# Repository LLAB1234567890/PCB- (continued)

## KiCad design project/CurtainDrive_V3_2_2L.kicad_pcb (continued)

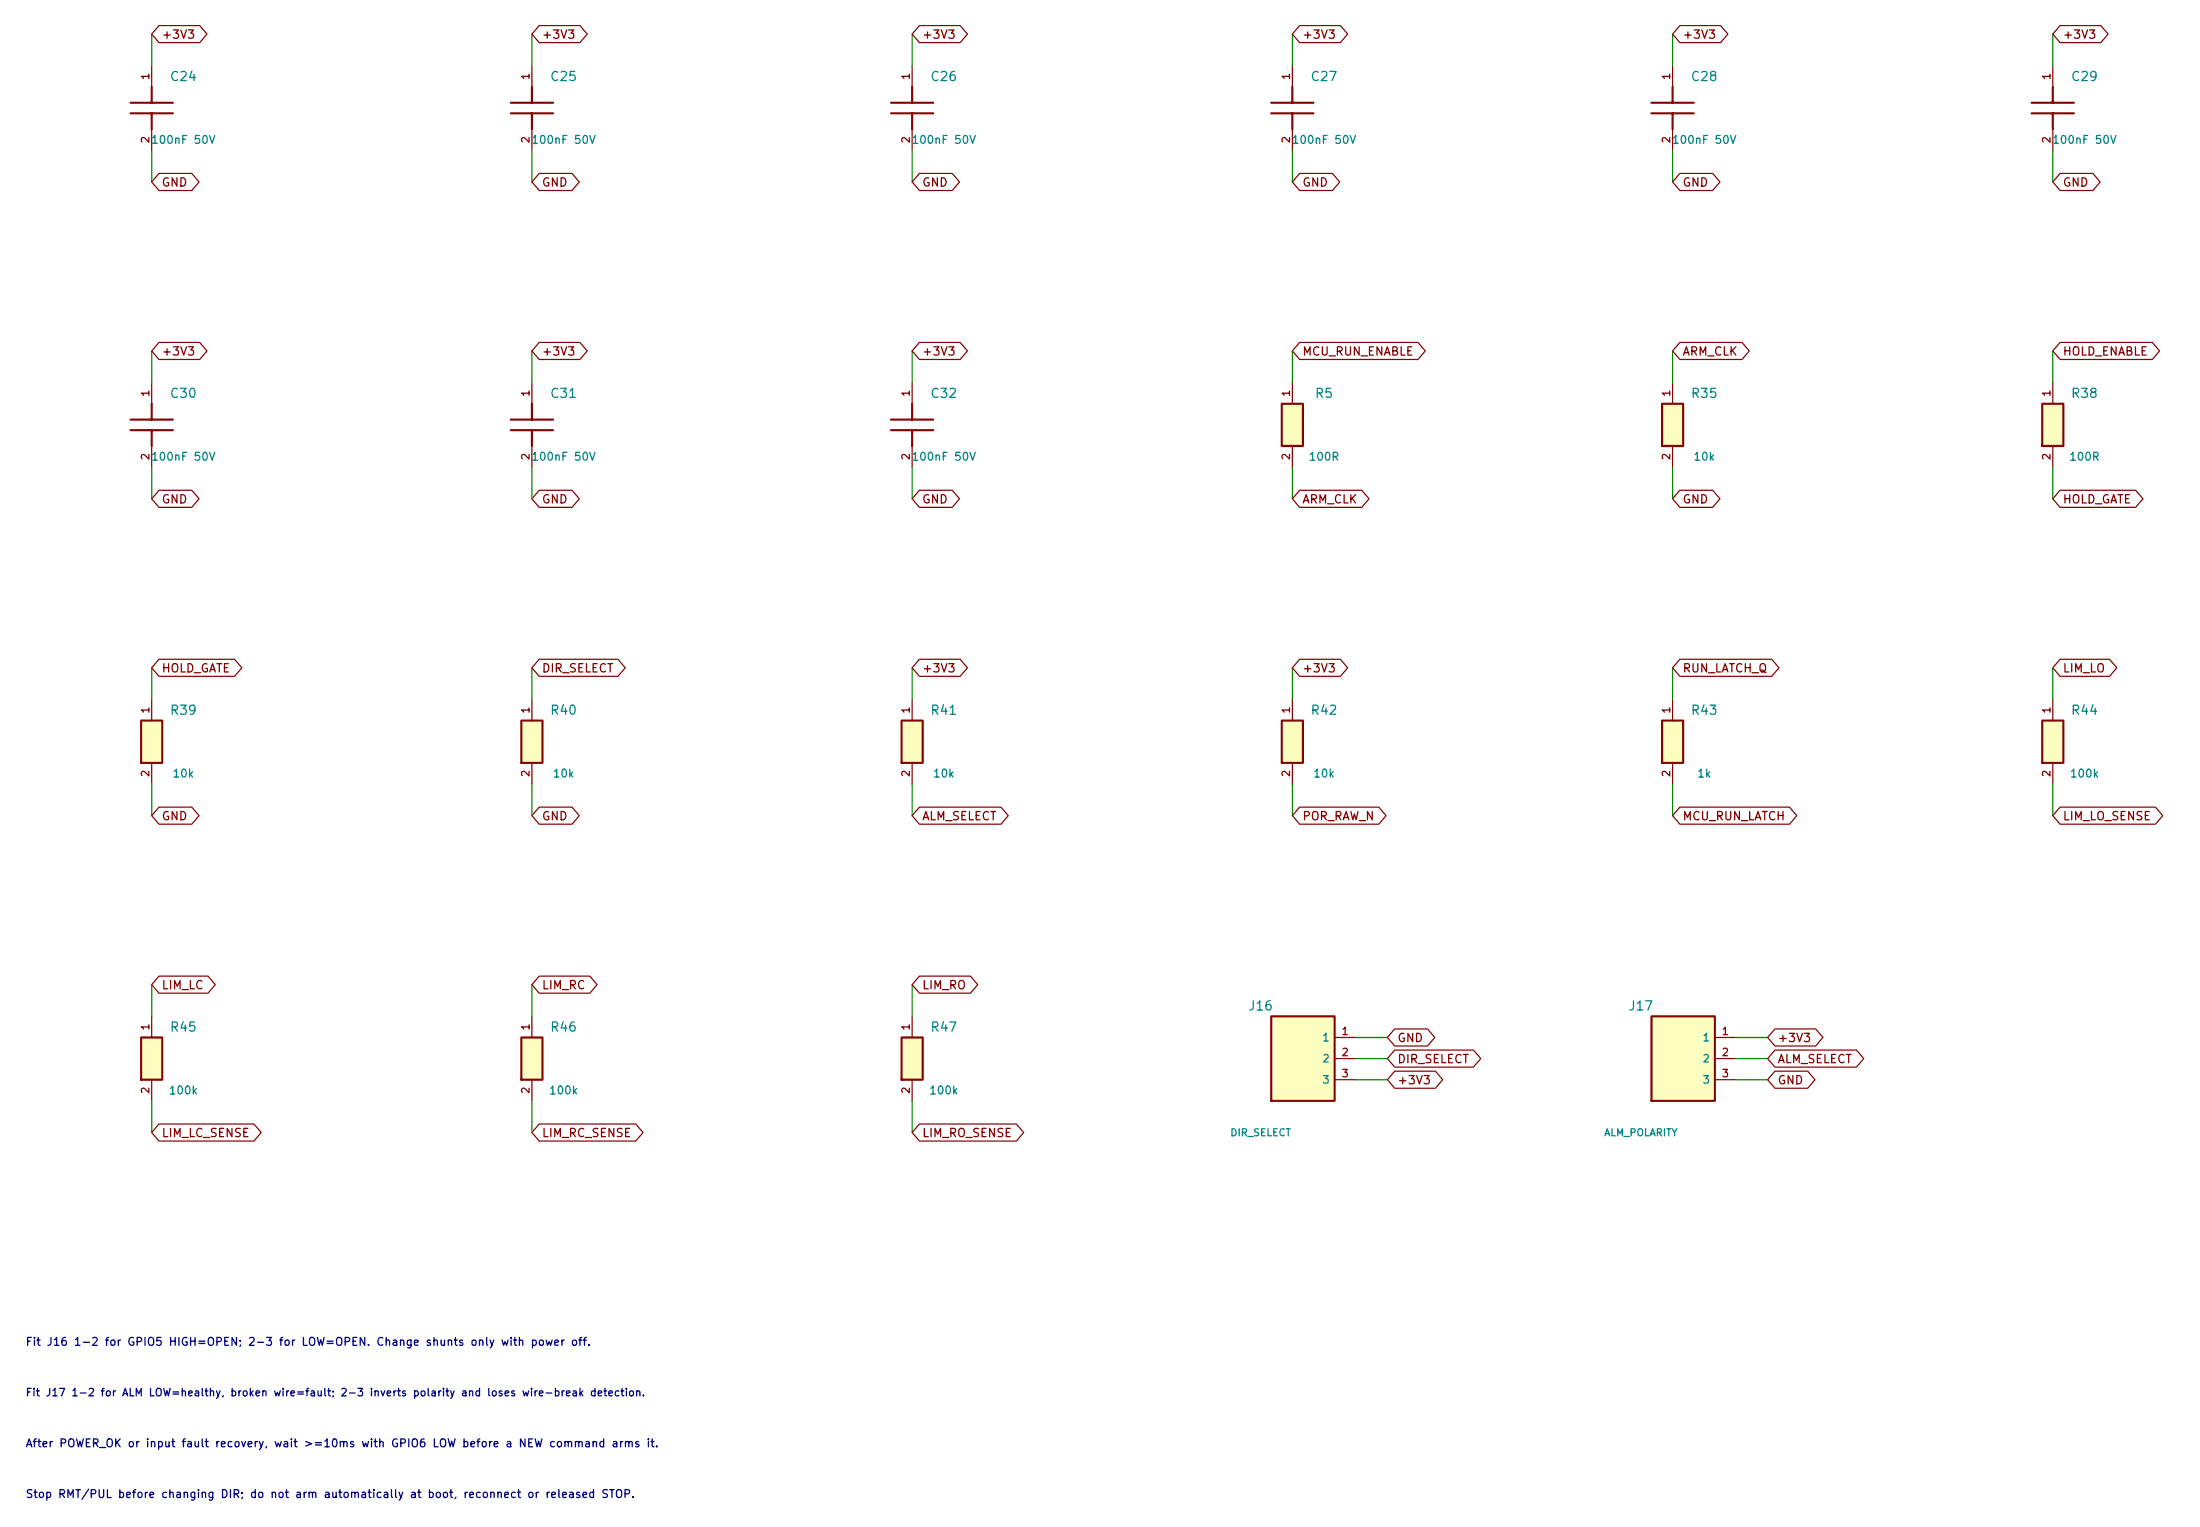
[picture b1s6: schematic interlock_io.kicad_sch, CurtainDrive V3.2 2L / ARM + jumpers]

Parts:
C24, C25, C26, C27, C28, C29, C30, C31, C32: 100nF 50V; C_0603_1608Metric; Voltage Rating 50V / X7R / 10%; Manufacturer Part CC0603KRX7R9BB104
J16: DIR_SELECT; PinHeader_1x03_P2.54mm_Vertical; Voltage Rating 2.54mm pitch; fit matching shunt separa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; Manufacturer Part 2.54mm 1x3 male header - exact MPN TBD
J17: ALM_POLARITY; PinHeader_1x03_P2.54mm_Vertical; Voltage Rating 2.54mm pitch; fit matching shunt separa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; Manufacturer Part 2.54mm 1x3 male header - exact MPN TBD
R5, R38: 100R; R_0603_1608Metric; Voltage Rating 1% / 0.1W; Manufacturer Part 0603WAF1000T5E
R35, R39, R40, R41, R42: 10k; R_0603_1608Metric; Voltage Rating 1% / 0.1W; Manufacturer Part 0603WAF1002T5E
R43: 1k; R_0603_1608Metric; Voltage Rating 1% / 0.1W; Manufacturer Part 0603WAF1001T5E
R44, R45, R46, R47: 100k; R_0603_1608Metric; Voltage Rating 1% / 0.1W; Manufacturer Part 0603WAF1003T5E

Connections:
+3V3: C24.1, C25.1, C26.1, C27.1, C28.1, C29.1, C30.1, C31.1, C32.1, J16.3, J17.1, R41.1, R42.1; also elsewhere on the board
ALM_SELECT: J17.2, R41.2; also elsewhere on the board
ARM_CLK: R5.2, R35.1; also elsewhere on the board
DIR_SELECT: J16.2, R40.1; also elsewhere on the board
GND: C24.2, C25.2, C26.2, C27.2, C28.2, C29.2, C30.2, C31.2, C32.2, J16.1, J17.3, R35.2, R39.2, R40.2; also elsewhere on the board
HOLD_ENABLE: R38.1; also elsewhere on the board
HOLD_GATE: R38.2, R39.1; also elsewhere on the board
LIM_LC: R45.1; also elsewhere on the board
LIM_LC_SENSE: R45.2; also elsewhere on the board
LIM_LO: R44.1; also elsewhere on the board
LIM_LO_SENSE: R44.2; also elsewhere on the board
LIM_RC: R46.1; also elsewhere on the board
LIM_RC_SENSE: R46.2; also elsewhere on the board
LIM_RO: R47.1; also elsewhere on the board
LIM_RO_SENSE: R47.2; also elsewhere on the board
MCU_RUN_ENABLE: R5.1; also elsewhere on the board
MCU_RUN_LATCH: R43.2; also elsewhere on the board
POR_RAW_N: R42.2; also elsewhere on the board
RUN_LATCH_Q: R43.1; also elsewhere on the board

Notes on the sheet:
Stop RMT/PUL before changing DIR; do not arm automatically at boot, reconnect or released STOP.
Fit J16 1-2 for GPIO5 HIGH=OPEN; 2-3 for LOW=OPEN. Change shunts only with power off.
After POWER_OK or input fault recovery, wait >=10ms with GPIO6 LOW before a NEW command arms it.
Fit J17 1-2 for ALM LOW=healthy, broken wire=fault; 2-3 inverts polarity and loses wire-break detection.

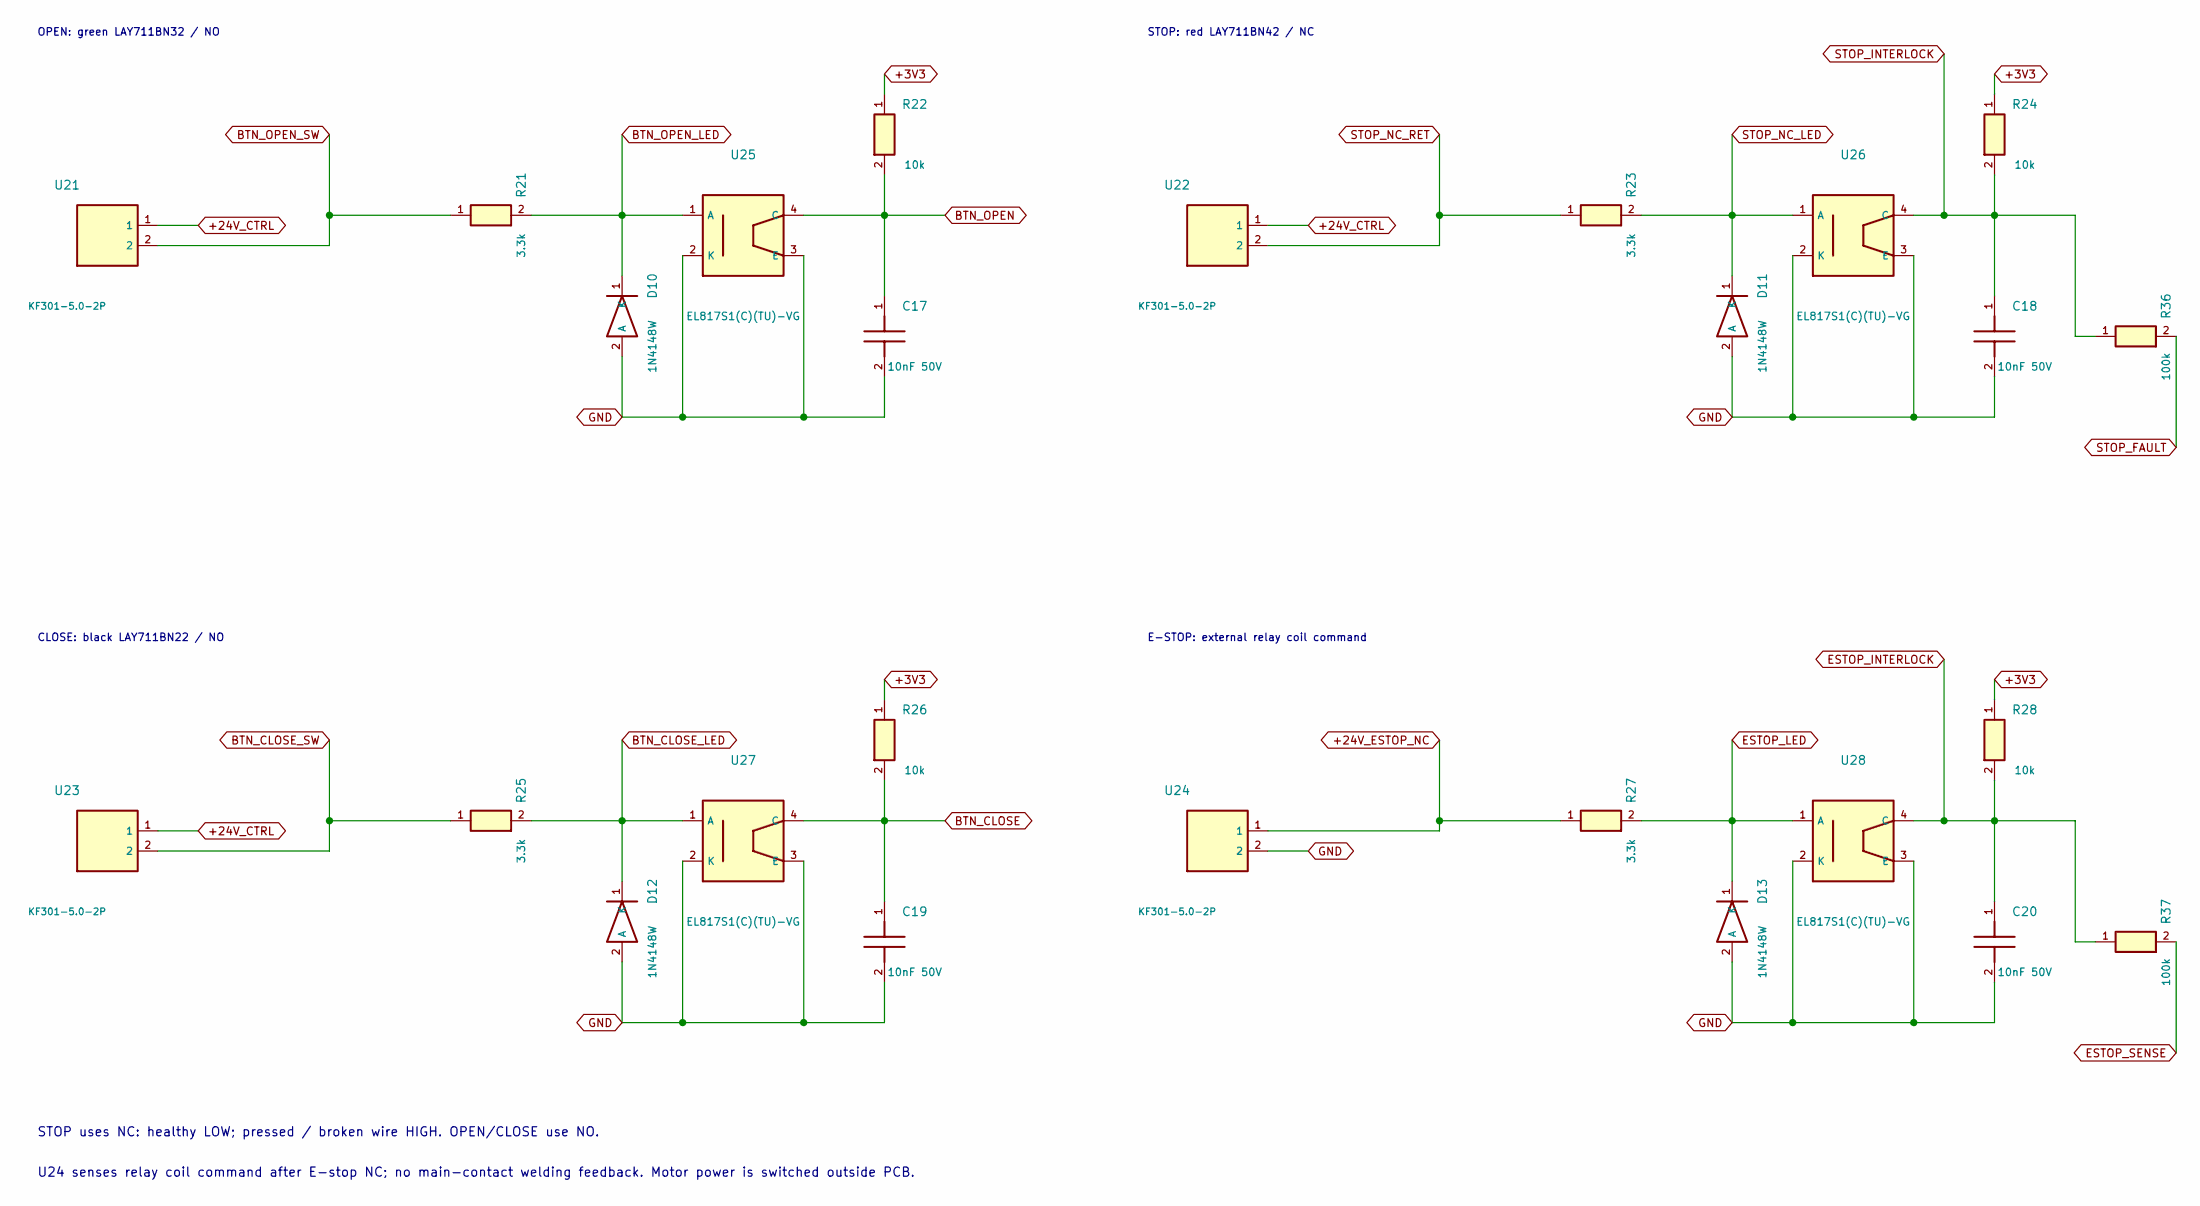
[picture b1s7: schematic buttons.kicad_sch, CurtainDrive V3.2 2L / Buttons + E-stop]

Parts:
C17, C18, C19, C20: 10nF 50V; C_0603_1608Metric; Voltage Rating 50V / X7R / 10%; Manufacturer Part 0603B103K500NT
D10, D11, D12, D13: 1N4148W; D_SOD-123; Voltage Rating 75V / 150mA; Manufacturer Part 1N4148W
R21, R23, R25, R27: 3.3k; R_1210_3225Metric; Voltage Rating 5% / 0.5W; Manufacturer Part 1210W2J0332T5E
R22, R24, R26, R28: 10k; R_0603_1608Metric; Voltage Rating 1% / 0.1W; Manufacturer Part 0603WAF1002T5E
R36, R37: 100k; R_0603_1608Metric; Voltage Rating 1% / 0.1W; Manufacturer Part 0603WAF1003T5E
U21: KF301-5.0-2P; Source_U21; Manufacturer Part KF301-5.0-2P
U22: KF301-5.0-2P; Source_U22; Manufacturer Part KF301-5.0-2P
U23: KF301-5.0-2P; Source_U23; Manufacturer Part KF301-5.0-2P
U24: KF301-5.0-2P; Source_U24; Manufacturer Part KF301-5.0-2P
U25: EL817S1(C)(TU)-VG; Source_U25; Manufacturer Part EL817S1(C)(TU)-VG
U26: EL817S1(C)(TU)-VG; Source_U26; Manufacturer Part EL817S1(C)(TU)-VG
U27: EL817S1(C)(TU)-VG; Source_U27; Manufacturer Part EL817S1(C)(TU)-VG
U28: EL817S1(C)(TU)-VG; Source_U28; Manufacturer Part EL817S1(C)(TU)-VG

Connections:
+3V3: R22.1, R24.1, R26.1, R28.1; also elsewhere on the board
+24V_CTRL: U21.1, U22.1, U23.1; also elsewhere on the board
+24V_ESTOP_NC: R27.1, U24.1
BTN_CLOSE: C19.1, R26.2, U27.4 (C); also elsewhere on the board
BTN_CLOSE_LED: D12.1 (K), R25.2, U27.1 (A)
BTN_CLOSE_SW: R25.1, U23.2
BTN_OPEN: C17.1, R22.2, U25.4 (C); also elsewhere on the board
BTN_OPEN_LED: D10.1 (K), R21.2, U25.1 (A)
BTN_OPEN_SW: R21.1, U21.2
ESTOP_INTERLOCK: C20.1, R28.2, R37.1, U28.4 (C); also elsewhere on the board
ESTOP_LED: D13.1 (K), R27.2, U28.1 (A)
ESTOP_SENSE: R37.2; also elsewhere on the board
GND: C17.2, C18.2, C19.2, C20.2, D10.2 (A), D11.2 (A), D12.2 (A), D13.2 (A), U24.2, U25.2 (K), U25.3 (E), U26.2 (K), U26.3 (E), U27.2 (K), U27.3 (E), U28.2 (K), U28.3 (E); also elsewhere on the board
STOP_FAULT: R36.2; also elsewhere on the board
STOP_INTERLOCK: C18.1, R24.2, R36.1, U26.4 (C); also elsewhere on the board
STOP_NC_LED: D11.1 (K), R23.2, U26.1 (A)
STOP_NC_RET: R23.1, U22.2

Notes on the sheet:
STOP: red LAY711BN42 / NC
U24 senses relay coil command after E-stop NC; no main-contact welding feedback. Motor power is switched outside PCB.
CLOSE: black LAY711BN22 / NO
STOP uses NC: healthy LOW; pressed / broken wire HIGH. OPEN/CLOSE use NO.
E-STOP: external relay coil command
OPEN: green LAY711BN32 / NO

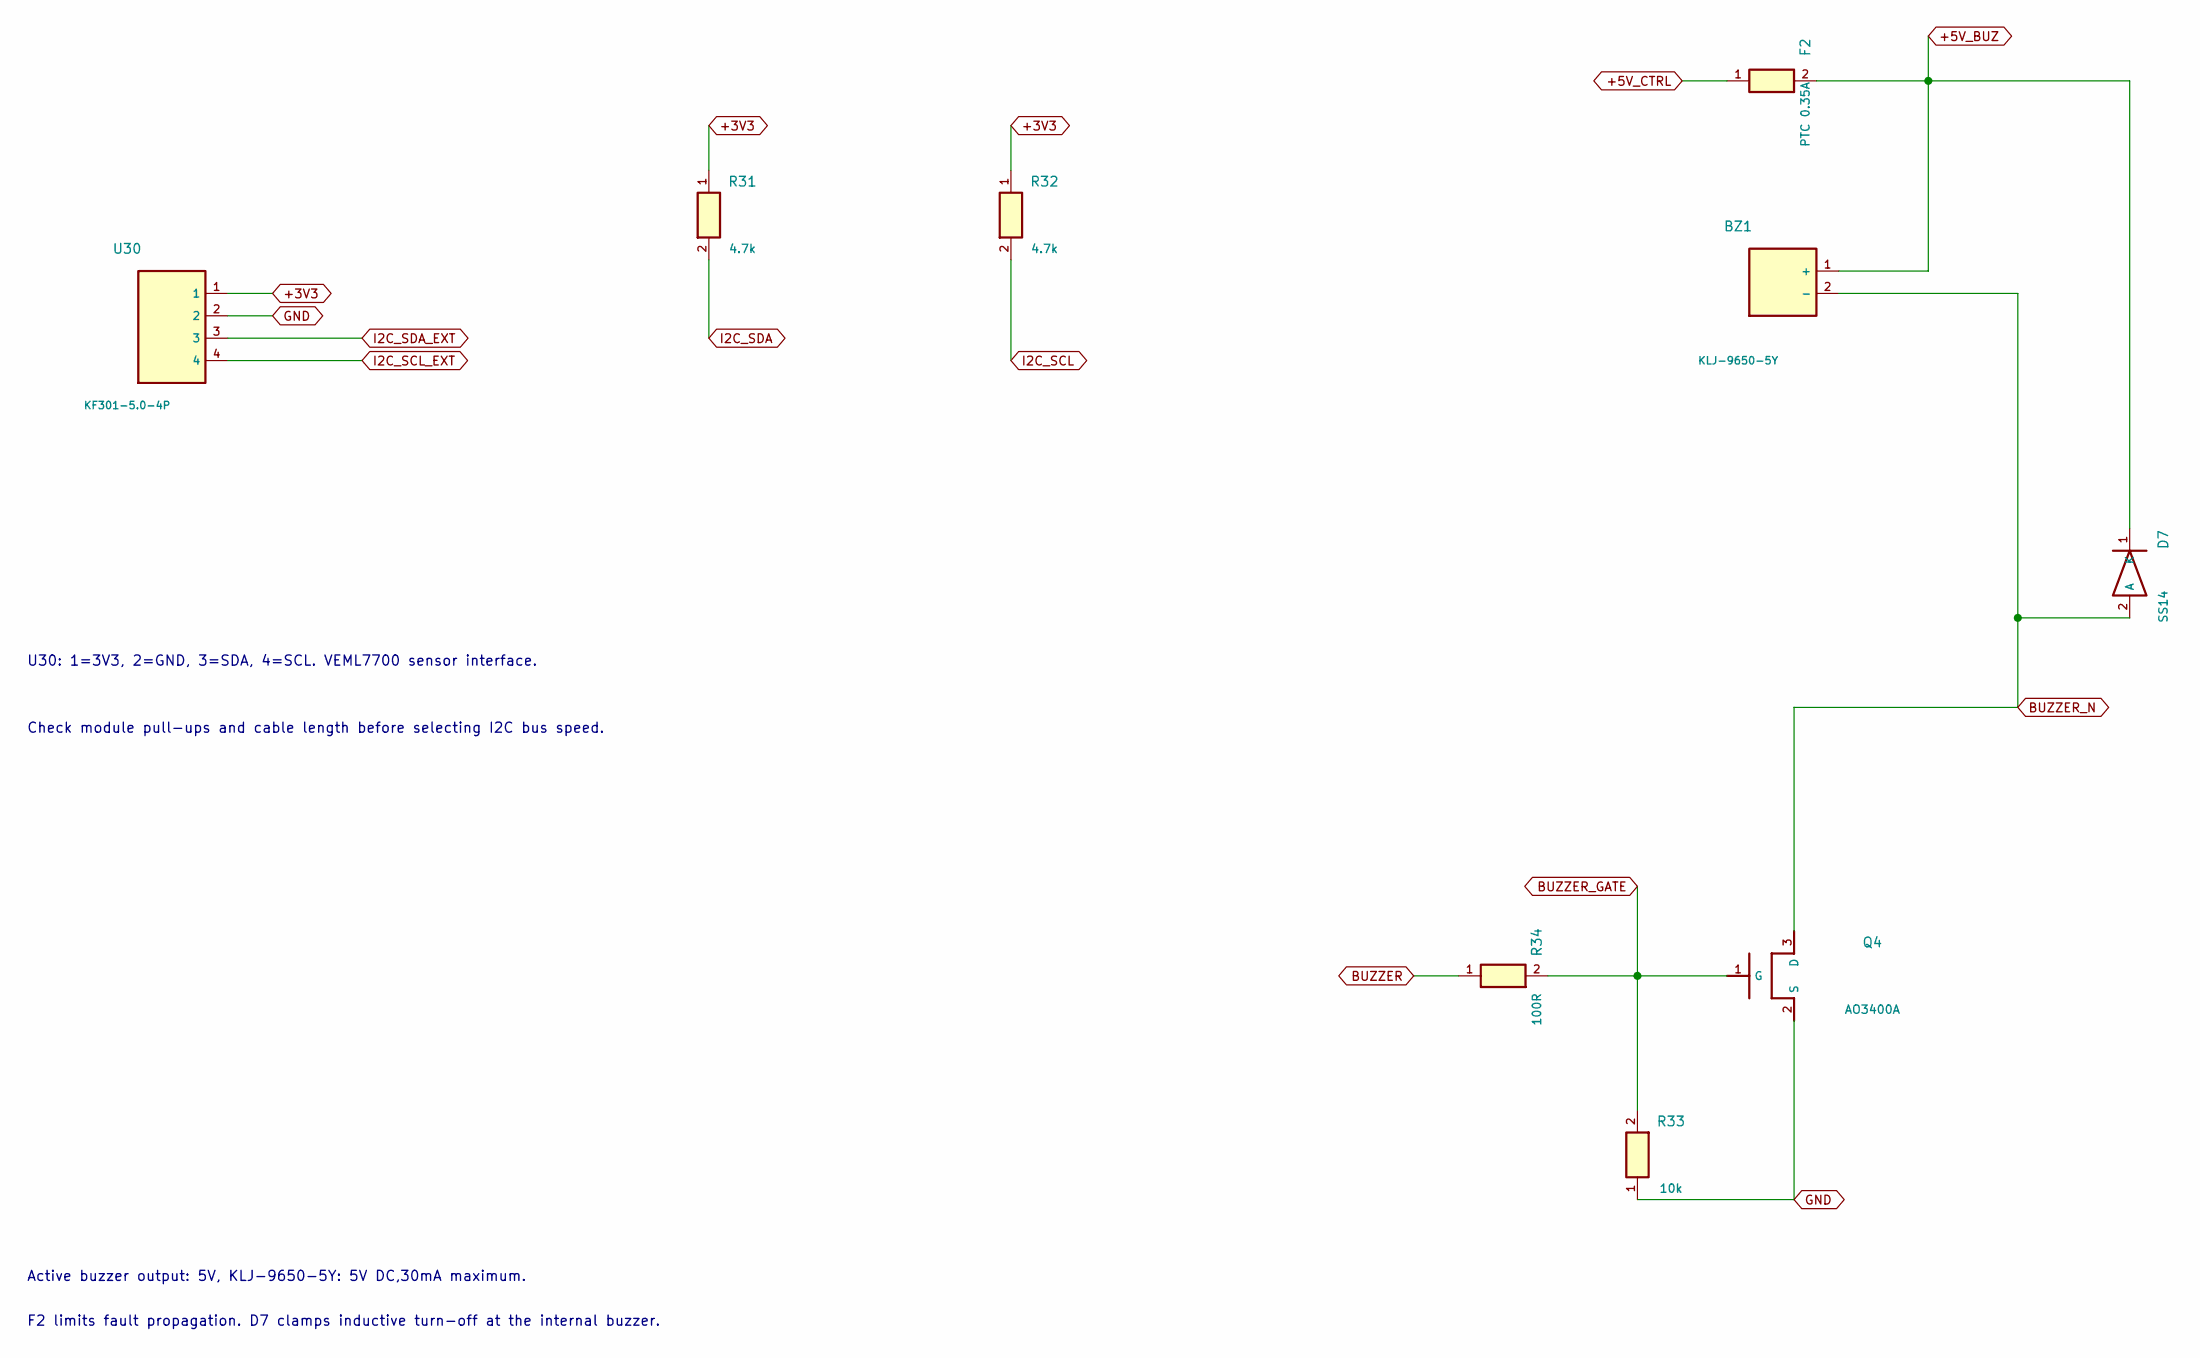
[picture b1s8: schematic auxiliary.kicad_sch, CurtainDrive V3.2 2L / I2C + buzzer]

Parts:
BZ1: KLJ-9650-5Y; KLJ_9650_5Y; Voltage Rating DC3–8V,5V nominal,30mA max; Manufacturer Part KLJ-9650-5Y
D7: SS14; D_SMA; Voltage Rating 40V / 1A; Manufacturer Part SS14
F2: PTC 0.35A; Fuse_1206_3216Metric; Voltage Rating 16V / hold0.35A / trip0.75A; Manufacturer Part 1206L035/16YR
Q4: AO3400A; SOT-23; Voltage Rating 30V / Rds(max)48mOhm@2.5V; Manufacturer Part AO3400A
R31, R32: 4.7k; R_1210_3225Metric; Voltage Rating 5% / 0.5W; Manufacturer Part 1210W2J0472T5E
R33: 10k; R_0603_1608Metric; Voltage Rating 1% / 0.1W; Manufacturer Part 0603WAF1002T5E
R34: 100R; R_0603_1608Metric; Voltage Rating 1% / 0.1W; Manufacturer Part 0603WAF1000T5E
U30: KF301-5.0-4P; KF301_5_0_4P; Manufacturer Part KF301-5.0-4P

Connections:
+3V3: R31.1, R32.1, U30.1; also elsewhere on the board
+5V_BUZ: BZ1.1 (+), D7.1 (K), F2.2; also elsewhere on the board
+5V_CTRL: F2.1; also elsewhere on the board
BUZZER: R34.1; also elsewhere on the board
BUZZER_GATE: Q4.1 (G), R33.2, R34.2
BUZZER_N: BZ1.2 (-), D7.2 (A), Q4.3 (D)
GND: Q4.2 (S), R33.1, U30.2; also elsewhere on the board
I2C_SCL: R32.2; also elsewhere on the board
I2C_SCL_EXT: U30.4; also elsewhere on the board
I2C_SDA: R31.2; also elsewhere on the board
I2C_SDA_EXT: U30.3; also elsewhere on the board

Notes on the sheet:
Check module pull-ups and cable length before selecting I2C bus speed.
U30: 1=3V3, 2=GND, 3=SDA, 4=SCL. VEML7700 sensor interface.
F2 limits fault propagation. D7 clamps inductive turn-off at the internal buzzer.
Active buzzer output: 5V, KLJ-9650-5Y: 5V DC,30mA maximum.

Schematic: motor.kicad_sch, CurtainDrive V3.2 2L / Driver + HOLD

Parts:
C21: 10nF 50V; C_0603_1608Metric; Voltage Rating 50V / X7R / 10%; Manufacturer Part 0603B103K500NT
Q1, Q2, Q3: AO3400A; SOT-23; Voltage Rating 30V / Rds(max)48mOhm@2.5V; Manufacturer Part AO3400A
Q5: AO3400A; SOT-23; Voltage Rating 30V / Vgs +/-12V; Manufacturer Part AO3400A
R1, R3: 100R; R_0603_1608Metric; Voltage Rating 1% / 0.1W; Manufacturer Part 0603WAF1000T5E
R2, R4, R6, R29: 10k; R_0603_1608Metric; Voltage Rating 1% / 0.1W; Manufacturer Part 0603WAF1002T5E
R30: 100k; R_1210_3225Metric; Voltage Rating 1% / 0.5W; Manufacturer Part RC1210FR-07100KL
U18: KF301-5.0-3P; Source_U18; Manufacturer Part KF301-5.0-3P
U19: KF301-5.0-3P; Source_U19; Manufacturer Part KF301-5.0-3P
U20: KF301-5.0-2P; Source_J1; Manufacturer Part KF301-5.0-2P

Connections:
+3V3: R29.1; also elsewhere on the board
+5V_CTRL: R6.2, U18.1, U18.3, U19.2; also elsewhere on the board
DIR_GATE: Q2.1 (G), R3.2, R4.1
DISABLE_GATE: Q3.1 (G), Q5.3 (D), R6.1
GND: C21.2, Q1.2 (S), Q2.2 (S), Q3.2 (S), Q5.2 (S), R2.2, R4.2, U20.2; also elsewhere on the board
HOLD_GATE: Q5.1 (G); also elsewhere on the board
MCU_DIR: R3.1; also elsewhere on the board
MOTOR_ALM: C21.1, R30.2; also elsewhere on the board
MOTOR_ALM_RAW: R29.2, R30.1, U20.1; also elsewhere on the board
MOTOR_DIR_N: Q2.3 (D), U19.1
MOTOR_ENA_N: Q3.3 (D), U19.3
MOTOR_PUL_N: Q1.3 (D), U18.2
PUL_GATED: R1.1; also elsewhere on the board
STEP_GATE: Q1.1 (G), R1.2, R2.1

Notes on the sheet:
DIR: GPIO5; J16 selects OPEN polarity
With +5V_CTRL present, Q3 disables if 3V3 is absent. External E-stop cuts motor power.
HOLD_ENABLE: healthy E-stop + power-good. Normal STOP does not withdraw ENA.
PUL_GATED from hardware latch

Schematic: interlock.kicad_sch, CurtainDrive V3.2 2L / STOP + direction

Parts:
U34, U42: SN74LVC14APWR; TSSOP-14_4.4x5mm_P0.65mm; Voltage Rating 3.3V logic; check exact manufacturer pa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; Manufacturer Part SN74LVC14APWR
U35, U37, U39: SN74LVC08APWR; TSSOP-14_4.4x5mm_P0.65mm; Voltage Rating 3.3V logic; check exact manufacturer pa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; Manufacturer Part SN74LVC08APWR
U36: SN74LVC86APWR; TSSOP-14_4.4x5mm_P0.65mm; Voltage Rating 3.3V logic; check exact manufacturer pa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; Manufacturer Part SN74LVC86APWR
U38: SN74LVC32APWR; TSSOP-14_4.4x5mm_P0.65mm; Voltage Rating 3.3V logic; check exact manufacturer pa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; Manufacturer Part SN74LVC32APWR
U40: SN74LVC74APWR; TSSOP-14_4.4x5mm_P0.65mm; Voltage Rating 3.3V logic; check exact manufacturer pa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; Manufacturer Part SN74LVC74APWR
U41: TLV803EA30DBZR; SOT-23; Voltage Rating 3.08V nominal falling threshold; minimu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; Manufacturer Part TLV803EA30DBZR

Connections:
+3V3: U34.14 (VCC), U35.14 (VCC), U36.10 (3B), U36.14 (VCC), U37.14 (VCC), U38.14 (VCC), U39.14 (VCC), U40.2 (1D), U40.4 (1PRE_N), U40.10 (2PRE_N), U40.14 (VCC), U41.3 (VDD), U42.14 (VCC); also elsewhere on the board
ALM_BUFFERED: U36.4 (2A), U42.4 (2Y)
ALM_INVERTED: U42.2 (1Y), U42.3 (2A)
ALM_OK: U35.13 (4B), U36.6 (2Y)
ALM_SELECT: U36.5 (2B); also elsewhere on the board
ARM_CLK: U39.10 (3B), U40.3 (1CLK); also elsewhere on the board
BUTTON_OK: U35.8 (3Y), U35.12 (4A)
CLOSE_ALLOWED: U37.6 (2Y), U38.2 (1B)
CLOSE_DIR: U36.8 (3Y), U37.4 (2A)
CLOSE_OK: U35.6 (2Y), U37.5 (2B)
CTRL5_N: U42.10 (5Y); also elsewhere on the board
CTRL5_SENSE: U42.11 (5A); also elsewhere on the board
DIR_ALLOWED: U37.10 (3B), U38.3 (1Y)
DIR_SELECT: U36.2 (1B); also elsewhere on the board
ESTOP_INTERLOCK: U34.13 (6A); also elsewhere on the board
ESTOP_OK: U34.12 (6Y), U35.10 (3B), U39.4 (2A)
GND: U34.7 (GND), U35.7 (GND), U36.7 (GND), U36.12 (4A), U36.13 (4B), U37.7 (GND), U38.4 (2A), U38.5 (2B), U38.7 (GND), U38.9 (3A), U38.10 (3B), U38.12 (4A), U38.13 (4B), U39.7 (GND), U40.7 (GND), U40.11 (2CLK), U40.12 (2D), U40.13 (2CLR_N), U41.1 (GND), U42.7 (GND), U42.13 (6A); also elsewhere on the board
HOLD_ENABLE: U39.6 (2Y); also elsewhere on the board
LC_OK: U34.4 (2Y), U35.4 (2A)
LIM_LC: U34.3 (2A); also elsewhere on the board
LIM_LO: U34.1 (1A); also elsewhere on the board
LIM_RC: U34.5 (3A); also elsewhere on the board
LIM_RO: U34.9 (4A); also elsewhere on the board
LO_OK: U34.2 (1Y), U35.1 (1A)
MCU_DIR: U36.1 (1A); also elsewhere on the board
MCU_STEP: U37.12 (4A); also elsewhere on the board
MOTION_HEALTHY: U37.8 (3Y), U39.1 (1A)
MOTOR_ALM_RAW: U42.1 (1A); also elsewhere on the board
OPEN_ALLOWED: U37.3 (1Y), U38.1 (1A)
OPEN_DIR: U36.3 (1Y), U36.9 (3A), U37.1 (1A)
OPEN_OK: U35.3 (1Y), U37.2 (1B)
POR_INVERTED: U42.6 (3Y), U42.9 (4A)
POR_RAW_N: U41.2 (RESET_N), U42.5 (3A); also elsewhere on the board
POWER_OK: U39.2 (1B), U39.5 (2B), U42.8 (4Y)
PUL_GATED: U39.8 (3Y); also elsewhere on the board
RC_OK: U34.6 (3Y), U35.5 (2B)
RO_OK: U34.8 (4Y), U35.2 (1B)
RUN_CLR_N: U39.11 (4Y), U40.1 (1CLR_N)
RUN_LATCH_Q: U37.13 (4B), U40.5 (1Q); also elsewhere on the board
RUN_PRECLR_N: U39.3 (1Y), U39.12 (4A)
STATIC_OK: U35.11 (4Y), U37.9 (3A)
STEP_LATCHED: U37.11 (4Y), U39.9 (3A)
STOP_INTERLOCK: U34.11 (5A); also elsewhere on the board
STOP_OK: U34.10 (5Y), U35.9 (3A)
WDT_OK: U39.13 (4B); also elsewhere on the board

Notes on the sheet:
AND4
U40 CLR_N = motion inputs healthy AND POWER_OK AND WDT_OK. Timeout stops pulses while HOLD remains enabled.
XOR4
POR
DFF2
SCHMITT
Q1 gate = GPIO4 AND U40.Q AND GPIO6. GPIO6 stuck HIGH cannot auto-restart after fault clears.
OR4
After any hardware fault: CLR_N recovers but Q stays LOW until a fresh GPIO6 rising edge.
J16 defines DIR polarity. J17 defines ALM polarity; default expects normally conducting alarm output.

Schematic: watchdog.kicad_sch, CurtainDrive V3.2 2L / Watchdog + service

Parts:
C35, C36: 100nF 50V; C_0603_1608Metric; Voltage Rating X7R50V; Manufacturer Part CC0603KRX7R9BB104
D15: TPD2E2U06DRLR; SOT-553; Voltage Rating 5.5V stand-off;1.5pF typ; dual ESD; Manufacturer Part TPD2E2U06DRLR
J19: MCU_PWR_LINK; PinHeader_1x02_P2.54mm_Vertical; Voltage Rating 2.54mm removable shunt; Manufacturer Part B-2100S02P-A110
R57, R58, R60: 10k; R_0603_1608Metric; Voltage Rating 1% /0.1W; Manufacturer Part 0603WAF1002T5E
R59, R61, R62: 100R; R_0603_1608Metric; Voltage Rating 1% /0.1W; Manufacturer Part 0603WAF1000T5E
U45: TPS3431SDRBR; Texas_DRB0008A; Voltage Rating 1.8–6.5V; watchdog active at3V3; Manufacturer Part TPS3431SDRBR

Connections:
+3V3: C35.1, R57.1, R58.1, U45.1 (VDD), U45.5 (SET1); also elsewhere on the board
+5V_BUZ: C36.1; also elsewhere on the board
+5V_MCU: J19.2; also elsewhere on the board
+5V_MCU_FEED: J19.1; also elsewhere on the board
GND: C35.2, C36.2, D15.1 (NC), D15.2 (NC), D15.4 (GND), R60.2, U45.4 (GND), U45.9 (EP); also elsewhere on the board
I2C_SCL: R62.2; also elsewhere on the board
I2C_SCL_EXT: D15.5 (IO2), R62.1; also elsewhere on the board
I2C_SDA: R61.2; also elsewhere on the board
I2C_SDA_EXT: D15.3 (IO1), R61.1; also elsewhere on the board
MCU_RESET_N: U45.3 (EN); also elsewhere on the board
MCU_WDI: R59.1; also elsewhere on the board
WDI: R59.2, R60.1, U45.6 (WDI)
WDT_CWD: R57.2, U45.2 (CWD)
WDT_OK: R58.2, U45.7 (WDO), U45.8 (ENOUT); also elsewhere on the board

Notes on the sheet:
Hardware timeout clears RUN latch only; ordinary STOP/crash retains holding torque.
Firmware control task toggles GPIO47 every<=50ms; communication lease expiry stops feeding.
Do not feed from timer/ISR/RMT: frozen application must cause a real external timeout.
EN low/reset holds WDT_OK low; recovery requires fresh ARM edge, never auto restart.
USB powered debug: remove J19 shunt.24V operation: fit J19; do not dual-power DevKit.
Gravity pin order differs: module SDA/SCL/GND/VCC; carrier VCC/GND/SDA/SCL.
TPS3431: SET1=3V3, CWD=10k toVDD; timeout200ms typ(170-230ms).
